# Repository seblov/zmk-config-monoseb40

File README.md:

The MonoSeb40 is a simple board i made mostly to try making a Monoblock split and to try ZMK and wireless.

It ended up actually being pretty nice to type on!
It's a 40-key 12x4 layout and the keys are angled inwards at 10 degrees.
I wanted to make the board MX spaced, but realized after i sent for the PCBs to be manufactured that it was choc.

If you want to make this for yourself, be aware that the PCB is wired for a NiceNano clone and i am not a 100% sure if the pinouts are the same.
Therefore, either get the NiceNano clone or edit the PCB.

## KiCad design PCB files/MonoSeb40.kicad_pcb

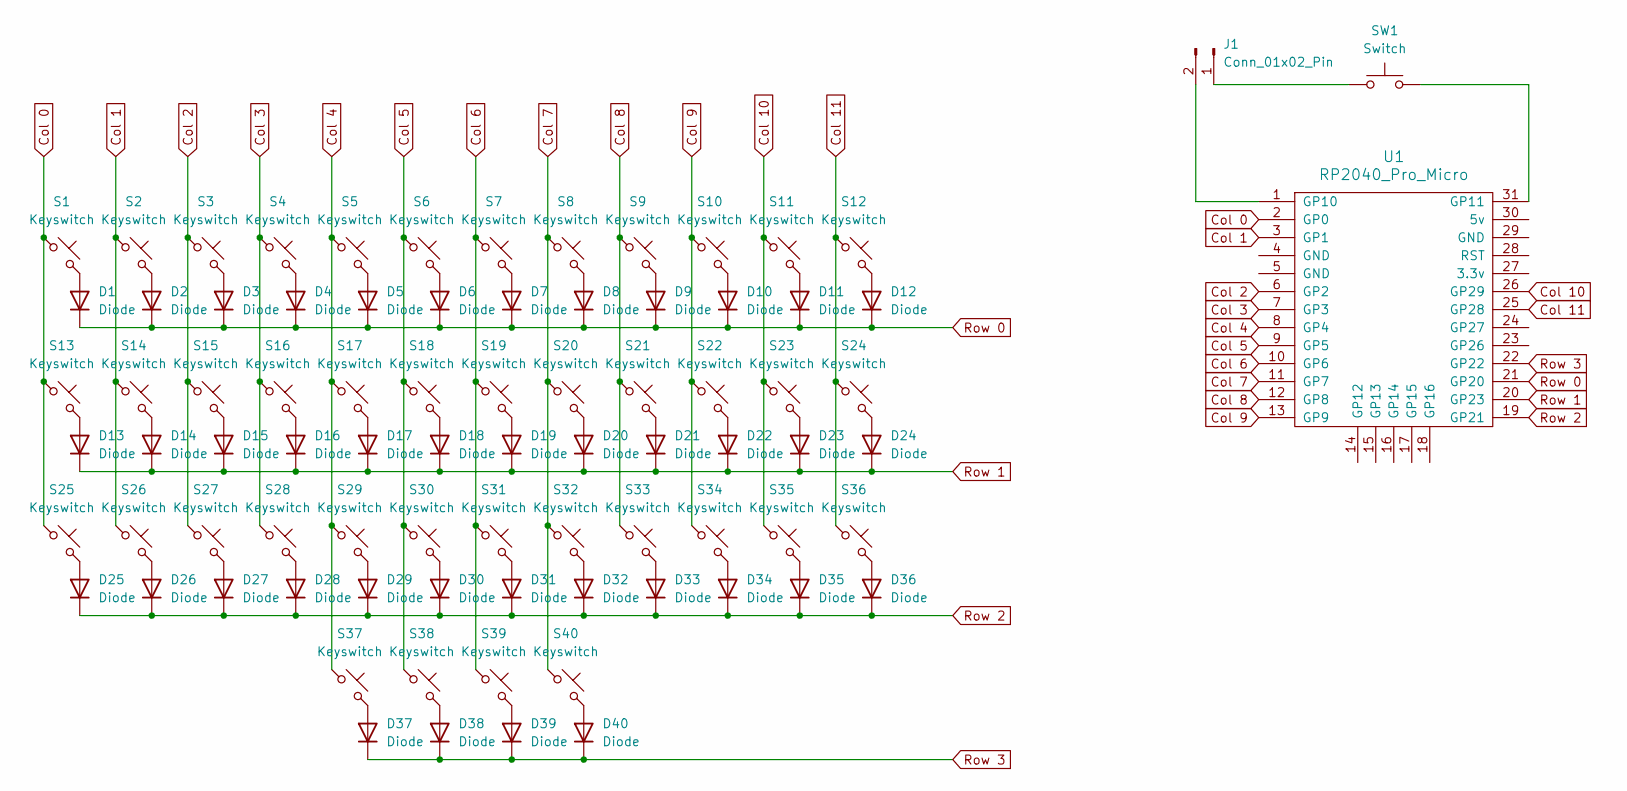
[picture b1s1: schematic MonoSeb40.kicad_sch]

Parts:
D1, D2, D3, D4, D5, D6, D7, D8, D9, D10, D11, D12, D13, D14, D15, D16, D17, D18, D19, D20, D21, D22, D23, D24, D25, D26, D27, D28, D29, D30, D31, D32, D33, D34, D35, D36, D37, D38, D39, D40: Diode; Diode_SOD-123
J1: Conn_01x02_Pin; JST_PH_S2B-PH-K_1x02_P2.00mm_Horizontal
S1, S2, S3, S4, S5, S6, S7, S8, S9, S10, S11, S12, S13, S14, S15, S16, S17, S18, S19, S20, S21, S22, S23, S24, S25, S26, S27, S28, S29, S30, S31, S32, S33, S34, S35, S36, S37, S38, S39, S40: Keyswitch; Hotswap_Choc_V1_1.00u
SW1: Switch; Switch_MSK12C02
U1: RP2040_Pro_Micro

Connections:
Col 0: S1.1, S13.1, S25.1, U1.2 (GP0)
Col 1: S2.1, S14.1, S26.1, U1.3 (GP1)
Col 2: S3.1, S15.1, S27.1, U1.6 (GP2)
Col 3: S4.1, S16.1, S28.1, U1.7 (GP3)
Col 4: S5.1, S17.1, S29.1, S37.1, U1.8 (GP4)
Col 5: S6.1, S18.1, S30.1, S38.1, U1.9 (GP5)
Col 6: S7.1, S19.1, S31.1, S39.1, U1.10 (GP6)
Col 7: S8.1, S20.1, S32.1, S40.1, U1.11 (GP7)
Col 8: S9.1, S21.1, S33.1, U1.12 (GP8)
Col 9: S10.1, S22.1, S34.1, U1.13 (GP9)
Col 10: S11.1, S23.1, S35.1, U1.26 (GP29)
Col 11: S12.1, S24.1, S36.1, U1.25 (GP28)
unnamed: D1.2 (A), S1.2
unnamed: D2.2 (A), S2.2
unnamed: D3.2 (A), S3.2
unnamed: D4.2 (A), S4.2
unnamed: D5.2 (A), S5.2
unnamed: D6.2 (A), S6.2
unnamed: D7.2 (A), S7.2
unnamed: D8.2 (A), S8.2
unnamed: D9.2 (A), S9.2
unnamed: D10.2 (A), S10.2
unnamed: D11.2 (A), S11.2
unnamed: D12.2 (A), S12.2
unnamed: D13.2 (A), S13.2
unnamed: D14.2 (A), S14.2
unnamed: D15.2 (A), S15.2
unnamed: D16.2 (A), S16.2
unnamed: D17.2 (A), S17.2
unnamed: D18.2 (A), S18.2
unnamed: D19.2 (A), S19.2
unnamed: D20.2 (A), S20.2
unnamed: D21.2 (A), S21.2
unnamed: D22.2 (A), S22.2
unnamed: D23.2 (A), S23.2
unnamed: D24.2 (A), S24.2
unnamed: D25.2 (A), S25.2
unnamed: D26.2 (A), S26.2
unnamed: D27.2 (A), S27.2
unnamed: D28.2 (A), S28.2
unnamed: D29.2 (A), S29.2
unnamed: D30.2 (A), S30.2
unnamed: D31.2 (A), S31.2
unnamed: D32.2 (A), S32.2
unnamed: D33.2 (A), S33.2
unnamed: D34.2 (A), S34.2
unnamed: D35.2 (A), S35.2
unnamed: D36.2 (A), S36.2
unnamed: D37.2 (A), S37.2
unnamed: D38.2 (A), S38.2
unnamed: D39.2 (A), S39.2
unnamed: D40.2 (A), S40.2
unnamed: J1.1, SW1.1
unnamed: J1.2, U1.1 (GP10)
unnamed: SW1.2, U1.31 (GP11)
Row 0: D1.1 (K), D2.1 (K), D3.1 (K), D4.1 (K), D5.1 (K), D6.1 (K), D7.1 (K), D8.1 (K), D9.1 (K), D10.1 (K), D11.1 (K), D12.1 (K), U1.21 (GP20)
Row 1: D13.1 (K), D14.1 (K), D15.1 (K), D16.1 (K), D17.1 (K), D18.1 (K), D19.1 (K), D20.1 (K), D21.1 (K), D22.1 (K), D23.1 (K), D24.1 (K), U1.20 (GP23)
Row 2: D25.1 (K), D26.1 (K), D27.1 (K), D28.1 (K), D29.1 (K), D30.1 (K), D31.1 (K), D32.1 (K), D33.1 (K), D34.1 (K), D35.1 (K), D36.1 (K), U1.19 (GP21)
Row 3: D37.1 (K), D38.1 (K), D39.1 (K), D40.1 (K), U1.22 (GP22)

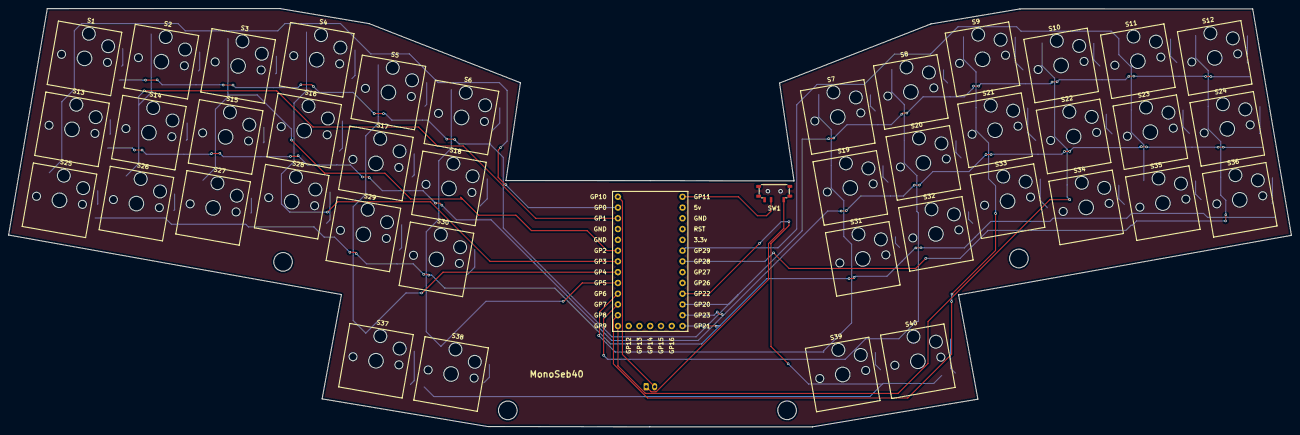
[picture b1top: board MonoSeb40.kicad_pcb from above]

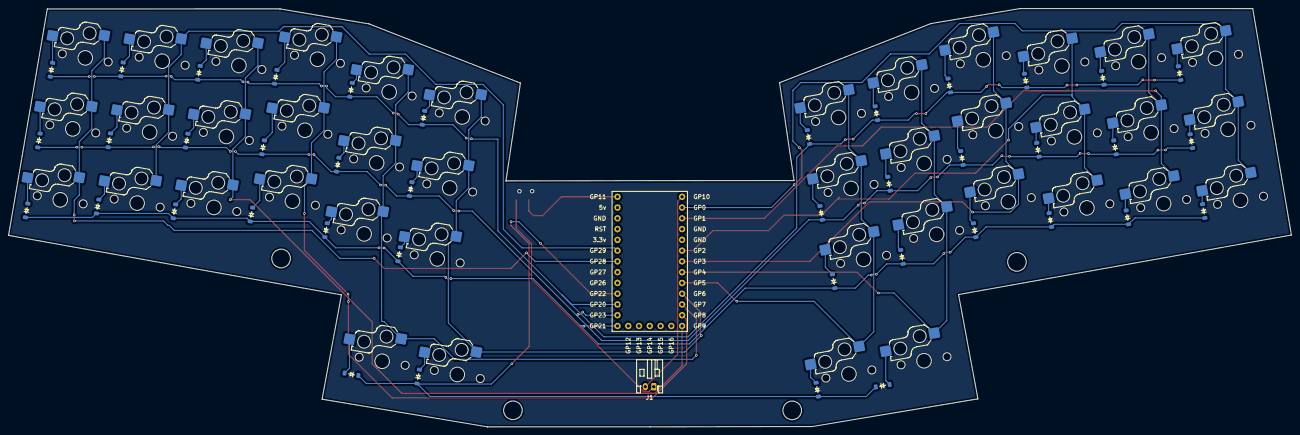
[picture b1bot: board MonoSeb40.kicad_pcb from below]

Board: 2 copper layers, 302.6 x 98.7 mm, 83 parts (41 on the bottom side), 59 nets.

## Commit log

2024-09-08 first go
2024-09-09 fixed space after komma on L10
2024-09-09 removed space on line 10
2024-09-09 added first row in keymap
2024-09-09 big stupid, added semicolons
2024-09-09 big stupid again, swapped bracket for curly ones
2024-09-09 tried something in keymap
2024-09-09 changed folder structure
2024-09-09 undid folder structure chsnges
2024-09-09 removed a space in kconfig.shield
2024-09-09 removed å. may have been seen as an invalid character
2024-09-10 added norwegian bokmål locale and reintroduced Å to keymap
2024-09-10 changed keys_nb include as string instead of <>
2024-09-10 implemented Å wrong, changed to definition name inside keys_nb.h
2024-09-10 tried adding a plain .keymap file to work with the online editor
2024-09-10 added info for ZMK editor and copied .keymap to config folder.
2024-09-10 moved info.json to config root folder
2024-09-10 Updated monoseb40.keymap
2024-09-10 changed folder structure to new standard
2024-09-10 undid folder structure change
2024-09-10 Changed the folder structure again to match the new ZMK docs
2024-09-10 updated layout for keymap editor to match the physical layout
2024-09-10 added a copy of keys_nb.h to root config folder
2024-09-11 Finished base layer
2024-09-11 finished layer 1 and 2
2024-09-16 troubleshooting, cheking if hold tap behaviours are bad
2024-09-16 changed column pos
2024-09-17 Changed the pull direction for the 4th row pin
2024-09-17 undid gpio pull direction change
2024-09-17 space + layer
2024-09-18 rewrote layers to accomodate norwegian
2024-09-18 greater than less than norwegian
2024-09-18 added ¨ on first layer
2024-09-18 changed minus to accomodate norwegian layout and added longer tap for super/alt
2024-09-18 changed media keys as k variant did not work
2024-09-18 added F11 to layer 2
2024-09-18 added bluetooth layer
2024-09-21 Added print files, PCB files and pictures
